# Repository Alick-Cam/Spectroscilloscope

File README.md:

# FYP-Repo
Software for Final Year Project 2020

Design and develop the necessary hardware and software systems needed to implement an
Oscilloscope and a Spectrum Analyser on a tablet/smartphone running the Android operating
system. To safeguard the handheld device it should communication via the Bluetooth with an
interfacing device that connects to the device under test.
Specifications (oscilloscope and spectrum analyser):
- Frequency: 0Hz – 20kHz.
- Voltage (AC and DC): 0V - 250V
- The device should be designed to use standard oscilloscope probes

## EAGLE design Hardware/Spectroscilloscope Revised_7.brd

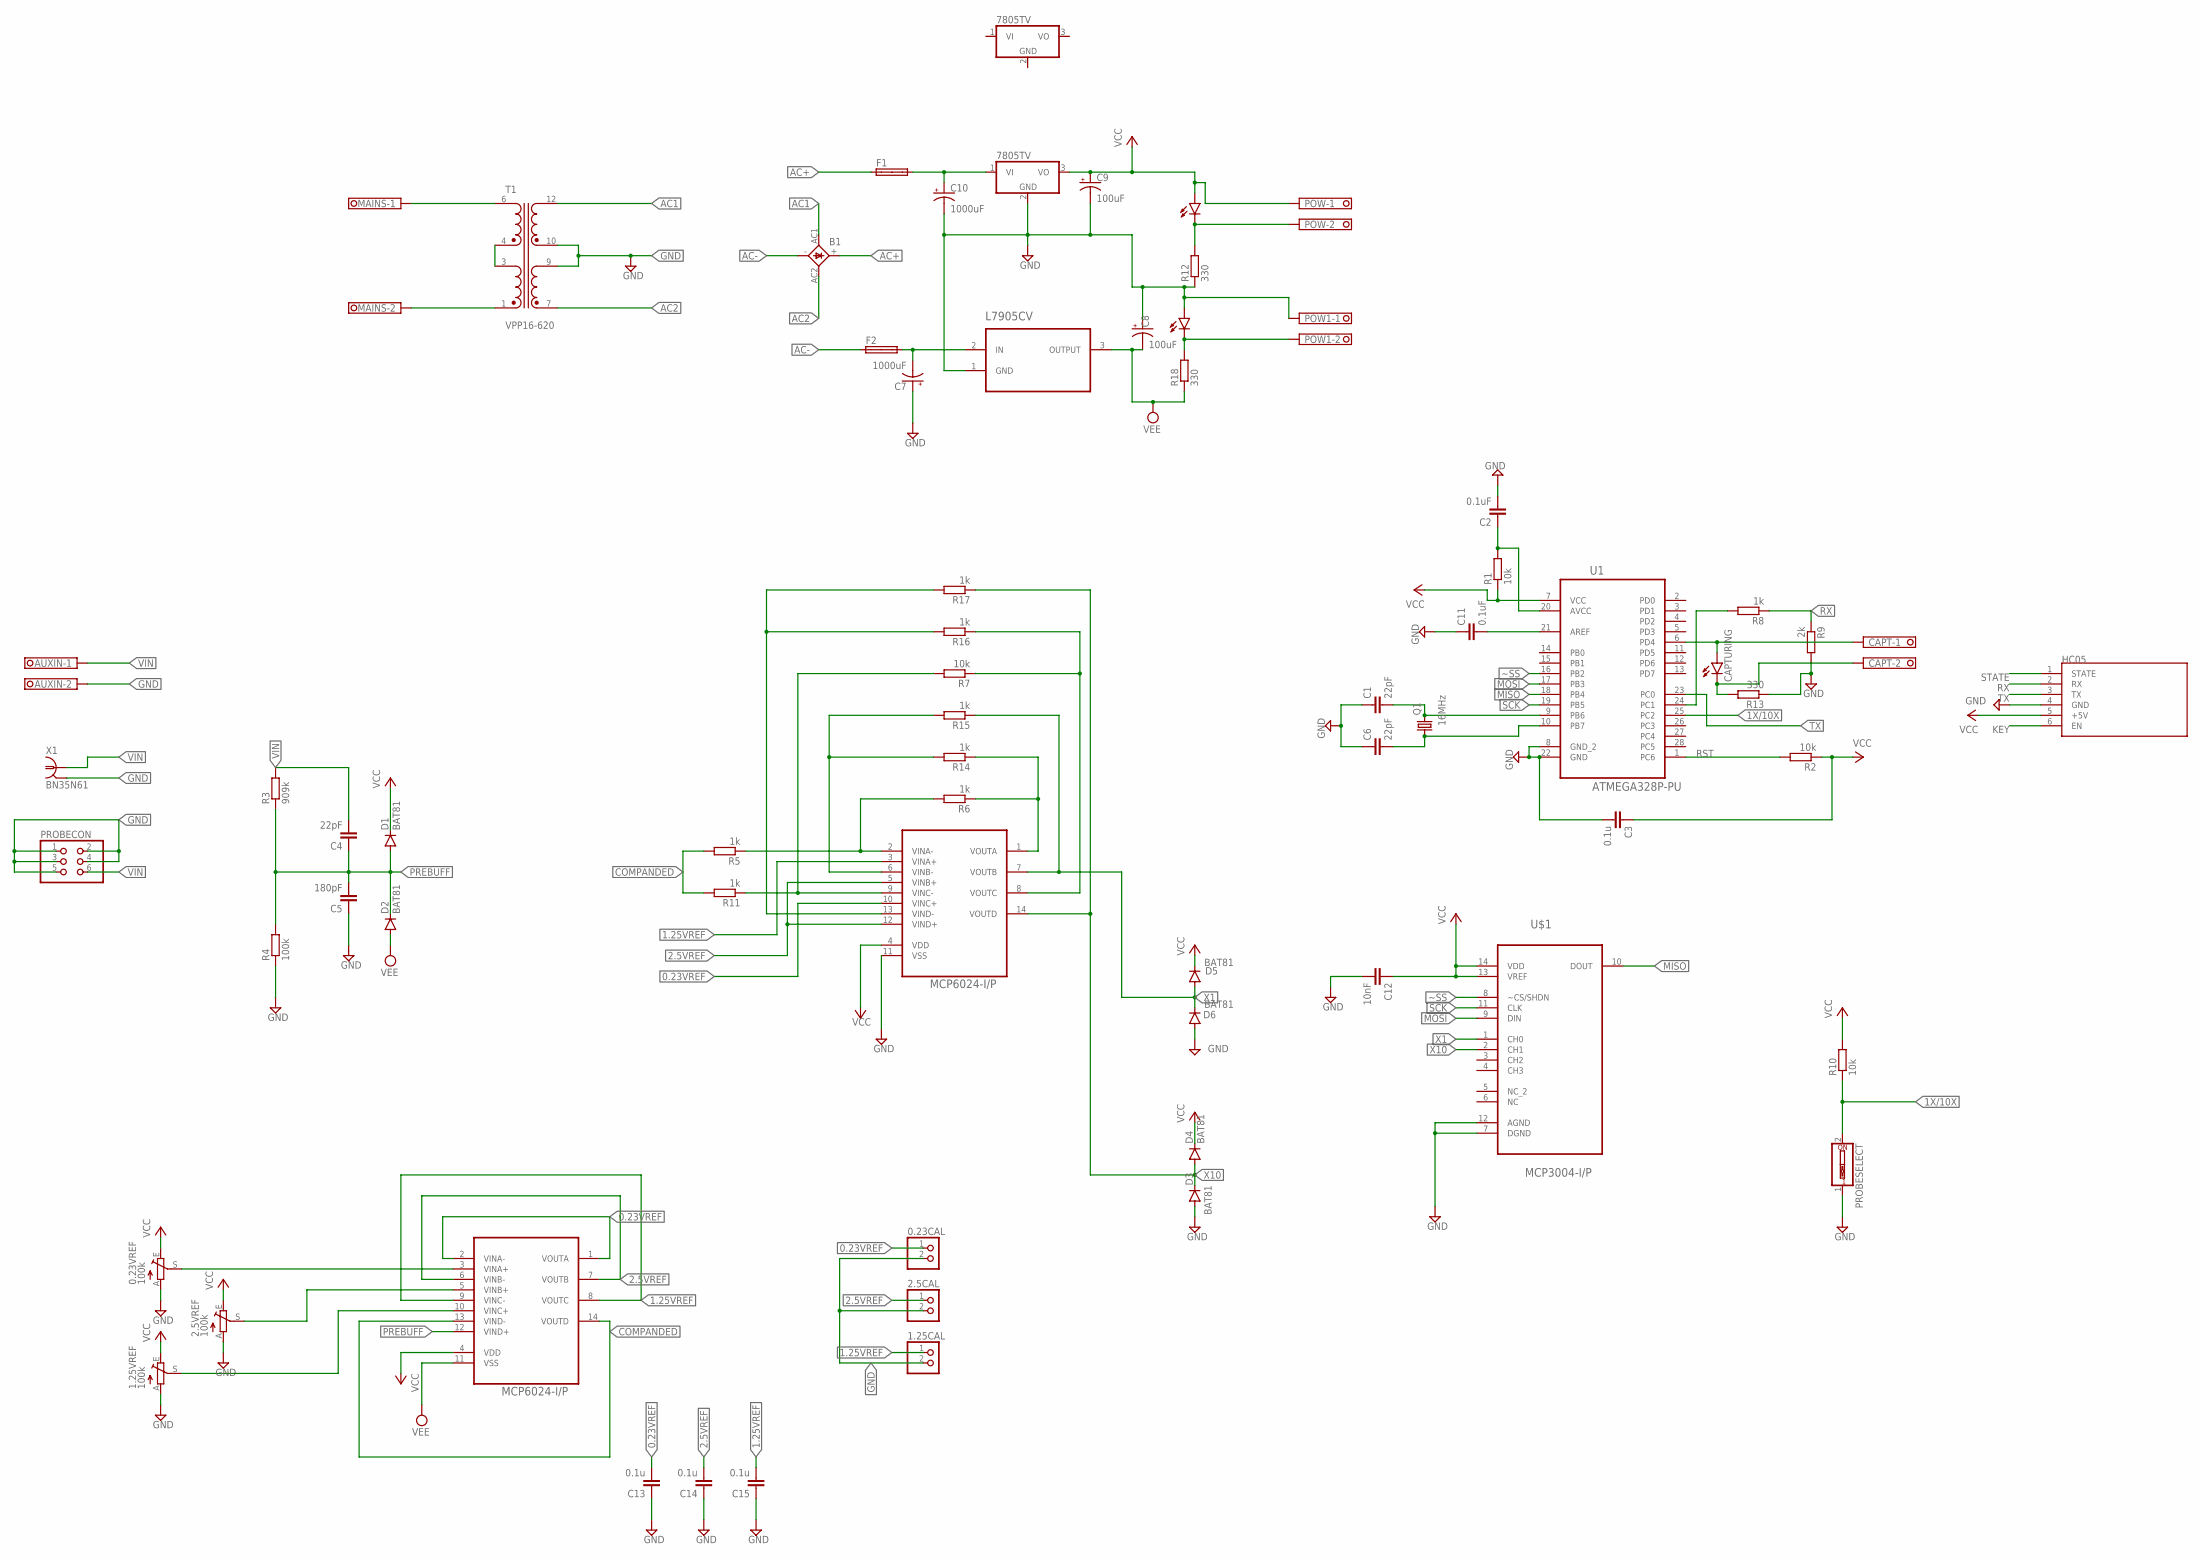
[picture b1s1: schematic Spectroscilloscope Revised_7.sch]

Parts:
0.23CAL, 1.25CAL, 2.5CAL: PINHD-1X2; 1X02
0.23VREF, 1.25VREF, 2.5VREF: 100k; B25P
AUXIN: TERMINAL-BLOCK-3.5MM-2-PIN-LONG-PAD; TERMINAL-BLOCK-2-PIN-3.5MM-LONG-PAD
B1: 2KBP
C1, C4, C6: 22pF; C050-024X044
C2, C11: 0.1uF; C050-024X044
C3, C13, C14, C15: 0.1u; C050-024X044
C5: 180pF; C050-024X044
C7, C10: 1000uF; E3,5-8
C8, C9: 100uF; E2,5-5
C12: 10nF; C050-024X044
CAPT: TERMINAL-BLOCK-3.5MM-2-PIN-LONG-PAD; TERMINAL-BLOCK-2-PIN-3.5MM-LONG-PAD
CAPTURING: LED5MM
D1, D2, D3, D4, D5, D6: BAT81; DO34-7
F1, F2: SHK20L
HC05: WIRELESS-BLUETOOTH-HC-05
IC1, IC2: 7805TV; TO220V
MAINS: TERMINAL-BLOCK-3.5MM-2-PIN-LONG-PAD; TERMINAL-BLOCK-2-PIN-3.5MM-LONG-PAD
POW, POW1: TERMINAL-BLOCK-3.5MM-2-PIN-LONG-PAD; TERMINAL-BLOCK-2-PIN-3.5MM-LONG-PAD
POWER, POWER1: LED5MM
PROBECON: PINHD-2X3; 2X03
PROBESELECT: SW_DIP-1; EDG-01
Q1: 16MHz; HC49U-V
Q2: L7905CV; TO254P450X1020X1935-3P
R1, R2, R7, R10: 10k; 0204/7
R3: 909k; 0204/7
R4: 100k; 0204/7
R5, R6, R8, R11, R14, R15, R16, R17: 1k; 0204/7
R9: 2k; 0204/7
R12, R13, R18: 330; 0204/7
T1: VPP16-620; XFMR_VPP16-620
U1: ATMEGA328P-PU; DIP254P762X457-28
U2, U3: MCP6024-I/P; DIP254P762X533-14
U$1: MCP3004-I/P; DIP254P762X432-14
X1: BN35N61; B35N61

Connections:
0.23VREF: 0.23CAL.1, C13.2, U2.10 (VINC+), U3.1 (VOUTA), U3.2 (VINA-)
1.25VREF: 1.25CAL.1, C15.2, U2.3 (VINA+), U3.8 (VOUTC), U3.9 (VINC-)
1X/10X: PROBESELECT.2, R10.1, U1.25 (PC2)
2.5VREF: 2.5CAL.1, C14.2, U2.5 (VINB+), U2.12 (VIND+), U3.6 (VINB-), U3.7 (VOUTB)
AC1: B1.AC1, T1.12
AC2: B1.AC2, T1.7
AC+: B1.+, F1.1A
AC-: B1.-, F2.1A
CAPTURING: CAPT.1, CAPTURING.A, U1.6 (PD4)
COMPANDED: R5.2, R11.2, U3.13 (VIND-), U3.14 (VOUTD)
GND: 0.23CAL.2, 0.23VREF.A, 1.25CAL.2, 1.25VREF.A, 2.5CAL.2, 2.5VREF.A, AUXIN.2, C1.1, C2.2, C3.2, C5.1, C6.1, C7.+, C8.+, C9.-, C10.-, C11.1, C12.2, C13.1, C14.1, C15.1, D3.A, D6.A, HC05.4 (GND), IC1.2 (GND), POW1.1, POWER1.A, PROBECON.1, PROBECON.2, PROBECON.3, PROBECON.4, PROBECON.5, PROBESELECT.1, Q2.1 (GND), R4.1, R9.2, R12.1, R13.1, T1.9, T1.10, U1.8 (GND_2), U1.22 (GND), U2.11 (VSS), U$1.7 (DGND), U$1.12 (AGND), X1.2, X1.3 (2), X1.4 (2), X1.5 (2)
KEY: HC05.6 (EN)
MAINS1: MAINS.1, T1.6
MAINS2: MAINS.2, T1.1
MISO: U1.18 (PB4), U$1.10 (DOUT)
MOSI: U1.17 (PB3), U$1.9 (DIN)
unnamed: C1.2, Q1.2, U1.9 (PB6)
unnamed: C6.2, Q1.1, U1.10 (PB7)
unnamed: 2.5VREF.S, U3.5 (VINB+)
unnamed: R6.1, R14.1, U2.1 (VOUTA)
unnamed: R5.1, R6.2, U2.2 (VINA-)
unnamed: C11.2, U1.21 (AREF)
unnamed: 1.25VREF.S, U3.10 (VINC+)
unnamed: C2.1, R1.2, U1.20 (AVCC)
unnamed: 0.23VREF.S, U3.3 (VINA+)
unnamed: T1.3, T1.4
unnamed: POW.2, POWER.K (C), R12.2
unnamed: CAPT.2, CAPTURING.K (C), R13.2
unnamed: R14.2, R15.2, U2.6 (VINB-)
unnamed: R7.2, R11.1, U2.9 (VINC-)
unnamed: R8.2, U1.24 (PC1)
unnamed: POW1.2, POWER1.K (C), R18.2
unnamed: R16.2, R17.2, U2.13 (VIND-)
unnamed: R7.1, R16.1, U2.8 (VOUTC)
NEG: C7.-, F2.2A, Q2.2 (IN)
POS: C10.+, F1.2A, IC1.1 (VI)
PREBUFF: C4.1, C5.2, D1.A, D2.C, R3.1, R4.2, U3.12 (VIND+)
RST: R2.2, U1.1 (PC6)
RX: HC05.2 (RX), R8.1, R9.1
SCK: U1.19 (PB5), U$1.11 (CLK)
STATE: HC05.1 (STATE)
TX: HC05.3 (TX), U1.23 (PC0)
VCC: 0.23VREF.E, 1.25VREF.E, 2.5VREF.E, C3.1, C9.+, C12.1, D1.C, D4.C, D5.C, HC05.5 (+5V), IC1.3 (VO), POW.1, POWER.A, R1.1, R2.1, R10.2, U1.7 (VCC), U2.4 (VDD), U3.4 (VDD), U$1.13 (VREF), U$1.14 (VDD)
VEE: C8.-, D2.A, Q2.3 (OUTPUT), R18.1, U3.11 (VSS)
VIN: AUXIN.1, C4.2, PROBECON.6, R3.2, X1.1
X1: D5.A, D6.C, R15.1, U2.7 (VOUTB), U$1.1 (CH0)
X10: D3.C, D4.A, R17.1, U2.14 (VOUTD), U$1.2 (CH1)
~SS: U1.16 (PB2), U$1.8 (~CS/SHDN)

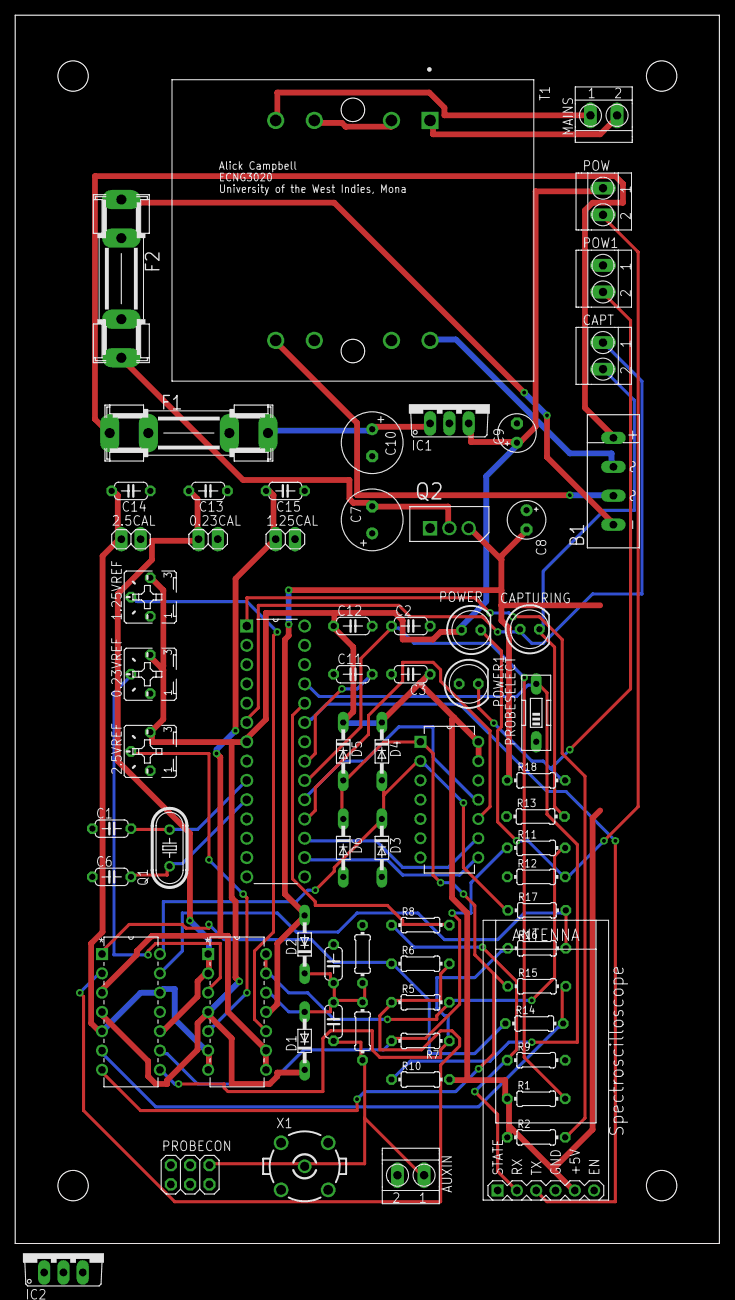
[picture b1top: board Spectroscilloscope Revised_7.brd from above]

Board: 2 copper layers, 92.7 x 161.7 mm, 69 parts (0 on the bottom side), 46 nets.

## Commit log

2020-12-22 This commit has the software prior to addition of threads
2020-12-22 Added basic app that graphs random values
2020-12-24 Changes to Send Sine Wave
2021-01-01 SpectroscilloscopeOmega is now graphing random values. Connect Button displays and when connected to spectroscilloscope, the Receive button displays
2021-01-12 MCP3004 Sample Code; Flow Chart for Android App
2021-01-12 Able to receive data within the 0 - 1023 range which is required for the sampled data
2021-01-13 Created New Project in which the fft thread will be tested
2021-01-13 Added Complex.java class
2021-01-13 Github Tutorial
2021-01-14 Added Fast Fourier Transform Thread to Spectroscilloscope v1.0
2021-01-20 Plotted 16 point FFT after receiving data over Bluetooth. TODO - plot actual data on a line chart after receiving over bluetooth
2021-01-21 Removed second Activity - OscilloscopeActivity.java
2021-01-21 Created App to understand Line Graph
2021-01-21 Now able to receive data over Bluetooth and plot it with a Line Chart TODO - remove bluetooth functionalities from main thread
2021-02-01 Updated Schematics - Added PCB - Generated Parts List - TODO: replace 3.5mm termiinal block with 5mm terminal block
2021-02-19 Schematics Update - Code Clean up - MCP3004 data Acquisition
2021-02-19 Floder Names
2021-03-05 Modified Send_Sine_Wave
2021-03-06 Edited configuration codes
2021-03-06 Placed Bluetooth Connection tasks in a seperate Thread
2021-03-27 Wroked on PCB, updated Schematic
2021-03-28 Max sample size = 512
2021-04-01 Updated Schematics
2021-04-20 Revised the Front end design - Final revision - multisim simulation works - Testing Breadboard April 21
2021-04-30 deleted two files that were not syncing with Google Drive
2021-05-30 Updated schematics - Further Update needed
2021-06-12 God be with me and this PCB
2021-06-14 Combined the two apps - more work to be done on controlling the whole process
2021-06-18 Combined both apps - Finallygit add .git add .! - Finishing touches needed
2021-06-22 Figure out why the FFT chart isnt showing
2021-06-22 Graphed and labeled, add highlights next
2021-06-22 Frequency Spectrum Graphing fully integrated - TODO - add indicators to Oscilloscope and listen for channel select
2021-06-26 Spectroscilloscope Prime v1 completed - time for optimization
2021-06-27 calibrated STEPSIZE and made sample rate dynamic
2021-06-29 Calibrated voltage references to match what is on the embedded system
2021-07-09 Revision to schematics for future upgrade
2021-07-09 Cleaned up repository

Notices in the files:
parts and their libraries:
diy-modules: Released under the Creative Commons Attribution 4.0 International License: http://creativecommons.org/licenses/by/4.0
